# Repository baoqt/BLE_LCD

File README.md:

# BLE_LCD
Using the RN4871 module, the microcontroller receives messages from a computer and displays text on the LCD.
___
### Primary goals
Establish connection with computer terminal or mobile device.

Reliably receive messages.

Stay within program memory limits, possibly offloading some code to the transmitter side.
### Planned additions
Removing the dedicated programming header if possible.

Switch over to serial USB programming for the PIC.

Add battery power and regulation.
___
### Relevant datasheets
BLE module:

http://ww1.microchip.com/downloads/en/DeviceDoc/RN4870-71-Bluetooth-Low-Energy-Module-Data-Sheet-DS50002489D.pdf

BLE module programming:

http://ww1.microchip.com/downloads/en/DeviceDoc/50002466B.pdf

PIC microcontroller:

http://ww1.microchip.com/downloads/en/devicedoc/pic16(l)f1831318323%20full%20featured%20low%20pin%20count%20microcontrollers%20with%20xlp_40001799d.pdf

LCD display:

http://www.newhavendisplay.com/specs/NHD-C12832A1Z-NSW-BBW-3V3.pdf

LCD display programming:

http://www.newhavendisplay.com/specs/NHD-C12832A1Z-NSW-BBW-3V3.pdf
### Images
First revision schematic:

First revision board:

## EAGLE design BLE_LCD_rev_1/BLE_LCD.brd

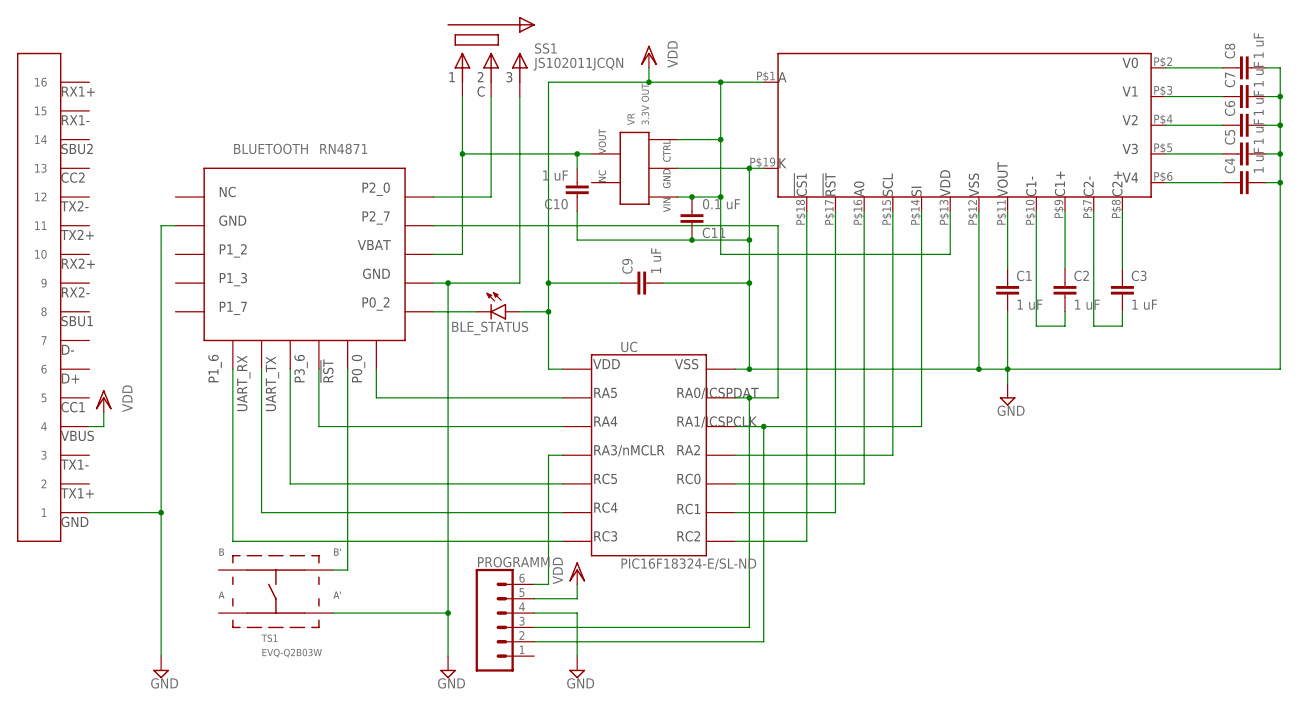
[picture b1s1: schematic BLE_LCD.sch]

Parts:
5VPOWER: USB-C
BLE_STATUS: LEDCHIPLED_1206; CHIPLED_1206
BLUETOOTH: RN4871
C1, C2, C3, C4, C5, C6, C7, C8, C9, C10: 1 uF; C0805
C11: 0.1 uF; C0805
LCD: NHD-C12832A1Z-NSW-BBW-3V3
PROGRAMM: CONN_06NO_SILK_FEMALE_PTH; 1X06_NO_SILK
SS1: JS102011JCQN
TS1: EVQ-Q2B03W
UC: PIC16F18324-E/SL-ND
VR: 3.3V OUT; TCR2EF33LM

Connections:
GND: 5VPOWER.A1 (1), 5VPOWER.A12 (1), 5VPOWER.B1 (1), 5VPOWER.B12 (1), BLUETOOTH.P$2, BLUETOOTH.P$13, C1.2, C4.2, C5.2, C6.2, C7.2, C8.2, C9.2, C10.1, C11.1, LCD.P$12, LCD.P$19, PROGRAMM.4, SS1.P$3, TS1.P$4, UC.P$14, VR.P$2
unnamed: C4.1, LCD.P$6
unnamed: C5.1, LCD.P$5
unnamed: C6.1, LCD.P$4
unnamed: C7.1, LCD.P$3
unnamed: C8.1, LCD.P$2
unnamed: C1.1, LCD.P$11
unnamed: C2.1, LCD.P$9
unnamed: C2.2, LCD.P$10
unnamed: C3.1, LCD.P$8
unnamed: C3.2, LCD.P$7
unnamed: LCD.P$15, UC.P$11
unnamed: LCD.P$16, UC.P$10
unnamed: LCD.P$17, UC.P$9
unnamed: LCD.P$18, UC.P$8
unnamed: LCD.P$14, PROGRAMM.2, UC.P$12
unnamed: BLUETOOTH.P$6, UC.P$7
unnamed: BLUETOOTH.P$7, UC.P$6
unnamed: PROGRAMM.6, UC.P$4
unnamed: BLUETOOTH.P$14, C10.2, SS1.P$1, VR.P$5
unnamed: BLUETOOTH.P$10, TS1.P$3
unnamed: BLUETOOTH.P$8, UC.P$5
unnamed: BLUETOOTH.P$9, UC.P$3
unnamed: BLUETOOTH.P$11, UC.P$2
unnamed: BLE_STATUS.C, BLUETOOTH.P$12
unnamed: BLUETOOTH.P$15, PROGRAMM.3, UC.P$13
unnamed: BLUETOOTH.P$16, SS1.P$2
VDD: 5VPOWER.A4 (4), 5VPOWER.A9 (4), 5VPOWER.B4 (4), 5VPOWER.B9 (4), BLE_STATUS.A, C9.1, C11.2, LCD.P$1, LCD.P$13, PROGRAMM.5, UC.P$1, VR.P$1, VR.P$3

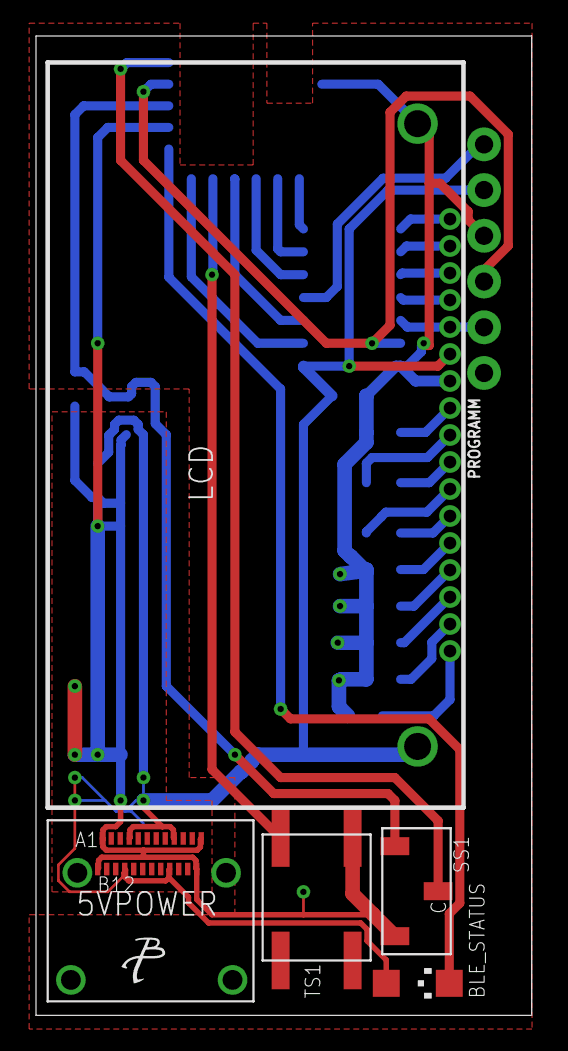
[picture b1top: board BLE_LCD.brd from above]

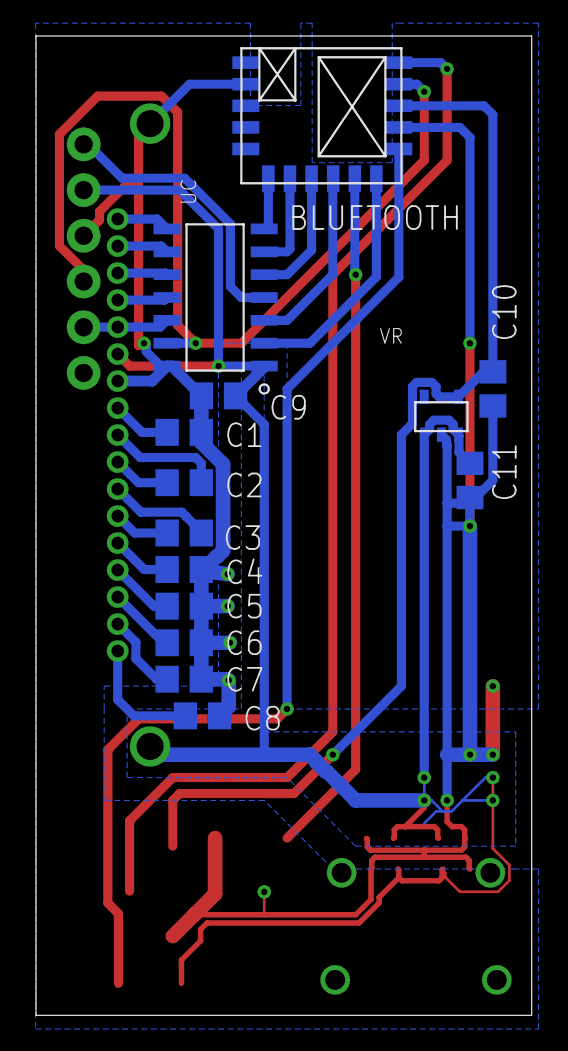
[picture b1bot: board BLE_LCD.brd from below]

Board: 2 copper layers, 27.5 x 54.4 mm, 20 parts (14 on the bottom side), 28 nets.

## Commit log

2019-05-28 Base code involving communication between the microcontroller and LCD display
2019-05-28 Reassigned pins according to PCB layout. Commented out code sections for ADC communication.
2019-05-28 Fixes some formatting in README.md
2019-06-02 Organized LCD functions into a header file. Cleaned up ADC functions and variables.
2019-06-02 Added images of first revision schematic and board.
2019-06-05 Added function to print strings. Letters 'U' through 'Z' cause the program to stall for unknown reasons.

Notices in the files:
parts and their libraries:
SparkFun-Connectors: Licensing: Creative Commons ShareAlike 4.0 International - https://creativecommons.org/licenses/by-sa/4.0
